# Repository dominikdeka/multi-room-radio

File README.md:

**enable Network at Boot**

`sudo raspi-config`
System Options->Network at Boot (enabled)

**print temperature alias**

`alias temp='vcgencmd measure_temp'`

**install gpio listener**

`sudo pip3 install websockets`
add to /etc/rc.local
`/home/pi/python_scripts/multi-room-radio/start.sh &> /tmp/rc.local.log`

**install mopidy**

https://docs.mopidy.com/en/latest/installation/debian/#install-from-apt-mopidy-com
```
sudo adduser mopidy video
```

https://mopidy.com/ext/
```
sudo python3 -m pip install Mopidy-TuneIn
sudo python3 -m pip install Mopidy-YouTube
sudo python3 -m pip install youtube-dl
sudo python3 -m pip install Mopidy-Iris
sudo python3 -m pip install Mopidy-Mobile
sudo python3 -m pip install Mopidy-SoundCloud
sudo python3 -m pip install Mopidy-Tidal

sudo chmod 755 /media/pi
copy mopidy.conf to /etc/mopidy/
```
https://docs.mopidy.com/en/latest/running/service/

```
pi@raspberrypi:~ $ aplay -L
(...)
hdmi:CARD=vc4hdmi,DEV=0
    vc4-hdmi, MAI PCM i2s-hifi-0
    HDMI Audio Output
(...)
```
--->
```
pi@raspberrypi:~ $ sudo vi /etc/mopidy/mopidy.conf
[audio]
output = alsasink device=hdmi:vc4hdmi
```

```
systemctl list-units --type=mount
```
--->
```
pi@raspberrypi:~ $ sudo vi /usr/lib/systemd/system/mopidy.service
[Unit]
(...)
After=media-pi-KINGSTON.mount
(...)
```

**crontab**

use backuped crontab

**hdmi blink**

turn it off

**websockets**

add content of https://github.com/dominikdeka/multi-room-radio/blob/master/index.html to
/usr/local/lib/python2.7/dist-packages/mopidy_mobile/www/index.html

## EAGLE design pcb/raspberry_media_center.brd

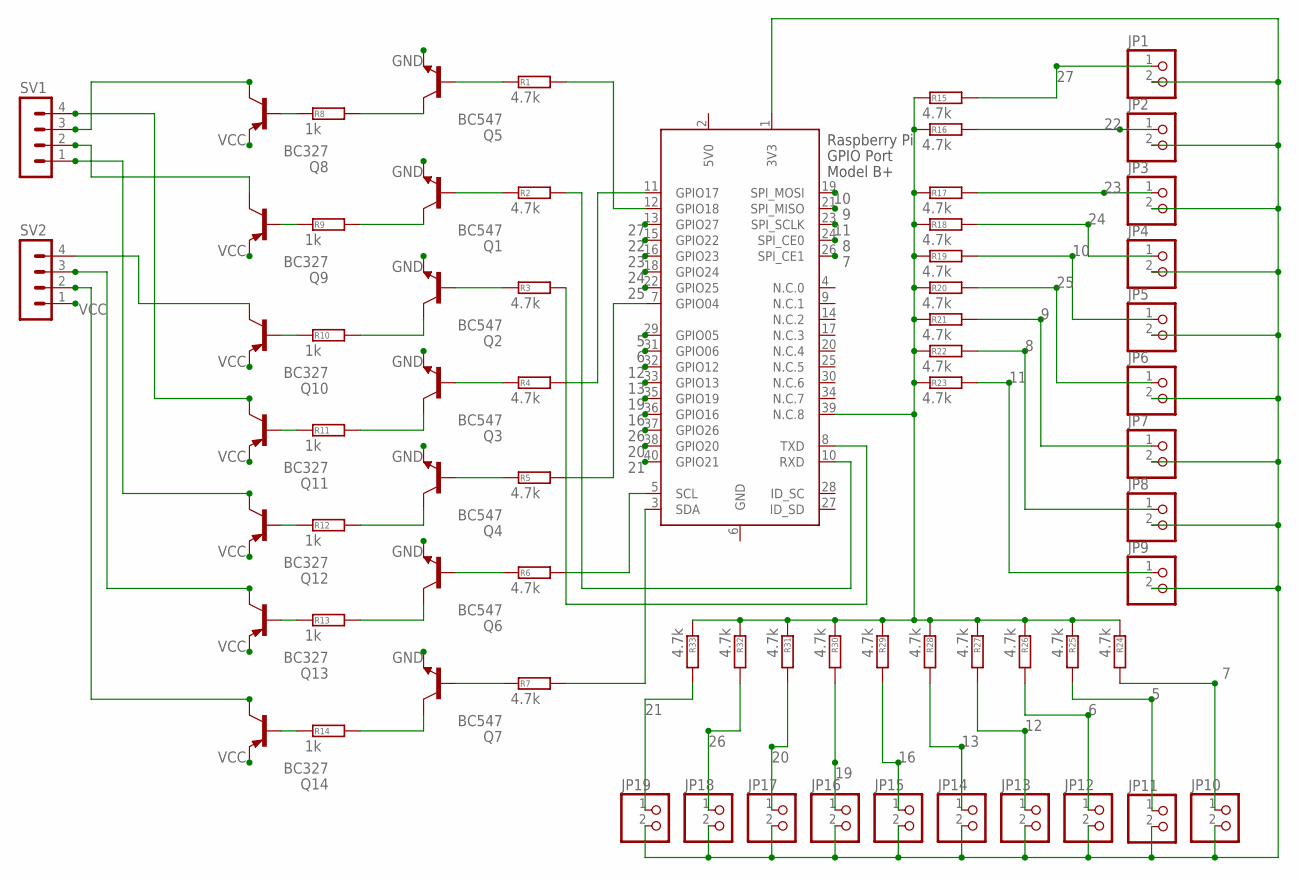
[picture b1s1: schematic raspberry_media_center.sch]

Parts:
JP1, JP2, JP3, JP4, JP5, JP6, JP7, JP8, JP9, JP10, JP11, JP12, JP13, JP14, JP15, JP16, JP17, JP18, JP19: PINHD-1X2; 1X02
Q1, Q2, Q3, Q4, Q5, Q6, Q7: BC547; TO92
Q8, Q9, Q10, Q11, Q12, Q13, Q14: BC327; TO92-EBC
R1, R2, R3, R4, R5, R6, R7: 4.7k; 0204/7
R8, R9, R10, R11, R12, R13, R14: 1k; 0204/7
R15, R16, R17, R18, R19, R20, R21, R22, R23, R24, R25, R26, R27, R28, R29, R30, R31, R32, R33: 4.7k; 0207/15
SV1, SV2: MA04-1
X1: RASPI_BOARD_B+_E0; RASPI_BOARD_B+_EDGES_0DRILL

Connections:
5: JP11.1, R25.2, X1.29 (GPIO05)
5V0: X1.2 (5V0)
6: JP12.1, R26.2, X1.31 (GPIO06)
7: JP10.1, R24.2, X1.26 (SPI_CE1)
8: JP8.1, R22.2, X1.24 (SPI_CE0)
9: JP7.1, R21.2, X1.21 (SPI_MISO)
10: JP5.1, R19.2, X1.19 (SPI_MOSI)
11: JP9.1, R23.2, X1.23 (SPI_SCLK)
12: JP13.1, R27.2, X1.32 (GPIO12)
13: JP14.1, R28.2, X1.33 (GPIO13)
16: JP15.1, R29.2, X1.36 (GPIO16)
19: JP16.1, R30.2, X1.35 (GPIO19)
20: JP17.1, R31.2, X1.38 (GPIO20)
21: JP19.1, R33.2, X1.40 (GPIO21)
22: JP2.1, R16.2, X1.15 (GPIO22)
23: JP3.1, R17.2, X1.16 (GPIO23)
24: JP4.1, R18.2, X1.18 (GPIO24)
25: JP6.1, R20.2, X1.22 (GPIO25)
26: JP18.1, R32.2, X1.37 (GPIO26)
27: JP1.1, R15.2, X1.13 (GPIO27)
GND: Q1.1 (E), Q2.1 (E), Q3.1 (E), Q4.1 (E), Q5.1 (E), Q6.1 (E), Q7.1 (E), X1.6 (GND)
unnamed: R7.2, X1.3 (SDA)
unnamed: R6.2, X1.5 (SCL)
unnamed: R5.2, X1.7 (GPIO04)
unnamed: R4.2, X1.11 (GPIO17)
unnamed: R3.2, X1.8 (TXD)
unnamed: R2.2, X1.10 (RXD)
unnamed: R1.2, X1.12 (GPIO18)
unnamed: Q5.2 (B), R1.1
unnamed: Q1.2 (B), R2.1
unnamed: Q2.2 (B), R3.1
unnamed: Q3.2 (B), R4.1
unnamed: Q4.2 (B), R5.1
unnamed: Q6.2 (B), R6.1
unnamed: Q7.2 (B), R7.1
unnamed: Q1.3 (C), R9.2
unnamed: Q5.3 (C), R8.2
unnamed: Q6.3 (C), R13.2
unnamed: Q4.3 (C), R12.2
unnamed: Q3.3 (C), R11.2
unnamed: Q2.3 (C), R10.2
unnamed: Q7.3 (C), R14.2
unnamed: Q8.B, R8.1
unnamed: Q9.B, R9.1
unnamed: Q10.B, R10.1
unnamed: Q11.B, R11.1
unnamed: Q12.B, R12.1
unnamed: Q13.B, R13.1
unnamed: Q14.B, R14.1
unnamed: R15.1, R16.1, R17.1, R18.1, R19.1, R20.1, R21.1, R22.1, R23.1, R24.1, R25.1, R26.1, R27.1, R28.1, R29.1, R30.1, R31.1, R32.1, R33.1, X1.39 (N.C.8)
unnamed: JP1.2, JP2.2, JP3.2, JP4.2, JP5.2, JP6.2, JP7.2, JP8.2, JP9.2, JP10.2, JP11.2, JP12.2, JP13.2, JP14.2, JP15.2, JP16.2, JP17.2, JP18.2, JP19.2, X1.1 (3V3)
unnamed: Q14.C, SV2.2
unnamed: Q13.C, SV2.3
unnamed: Q12.C, SV1.1
unnamed: Q11.C, SV1.4
unnamed: Q10.C, SV2.4
unnamed: Q8.C, SV1.3
unnamed: Q9.C, SV1.2
VCC: Q8.E, Q9.E, Q10.E, Q11.E, Q12.E, Q13.E, Q14.E, SV2.1

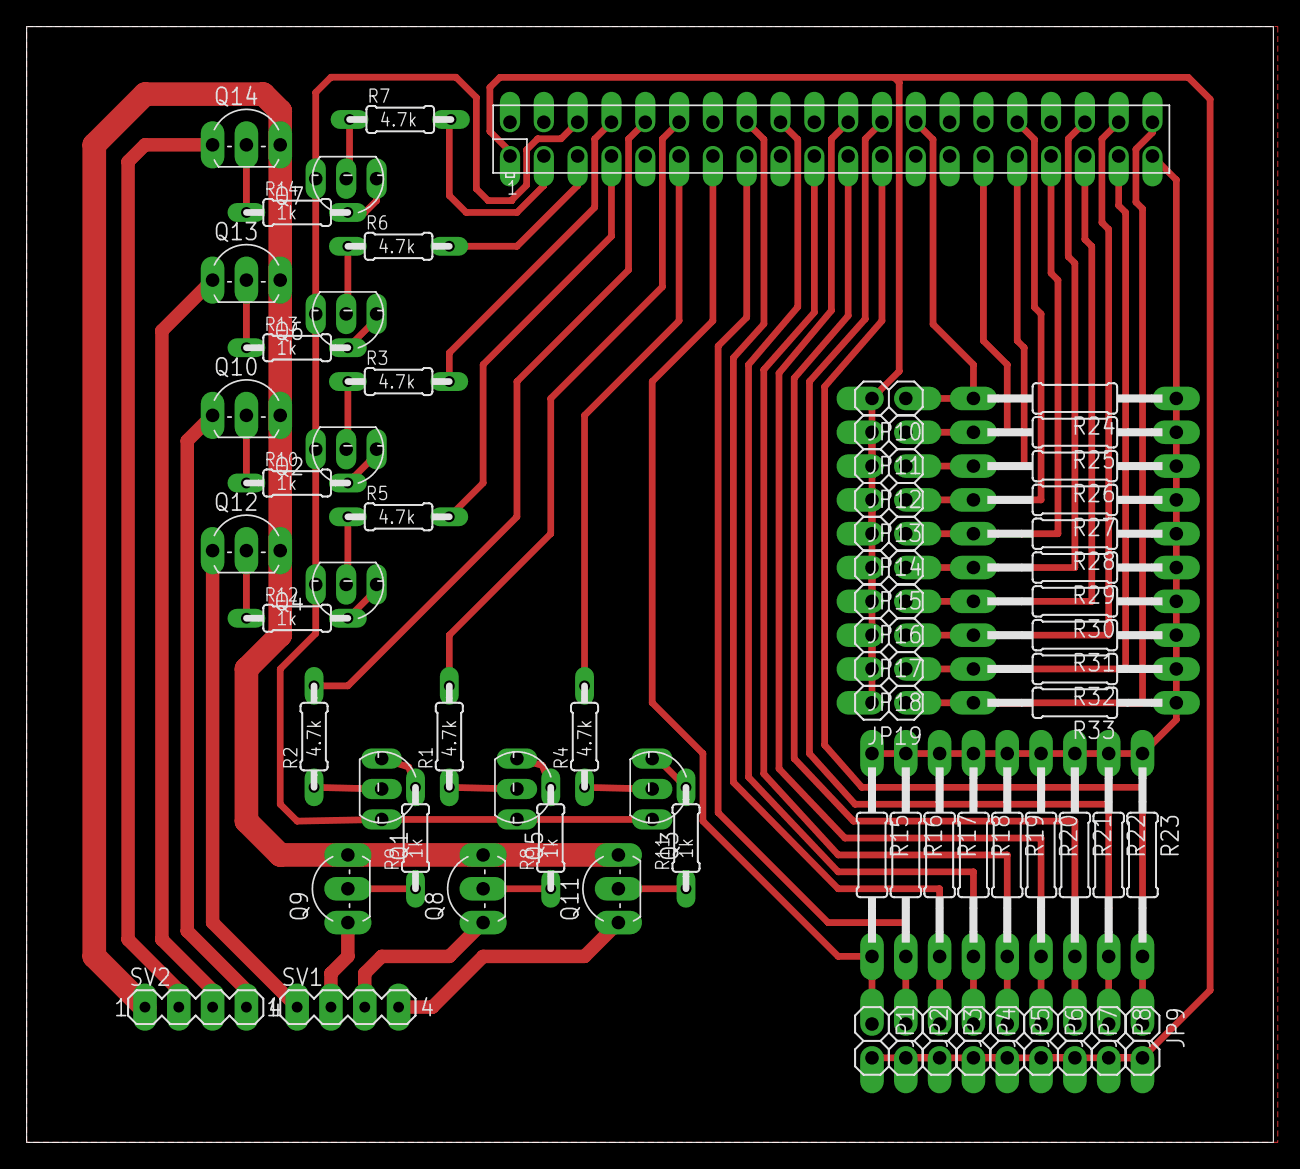
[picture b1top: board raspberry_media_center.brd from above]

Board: 2 copper layers, 93.7 x 83.8 mm, 69 parts (0 on the bottom side), 58 nets.

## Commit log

2018-06-18 websockets introduced
2018-08-17 setup + l&f
2018-08-31 start script added
2018-09-17 more functions
2018-09-18 mic function added
2018-09-24 new playlists features, startup script corrections
2019-03-27 wakeup added + fix
2019-11-04 new wakeup set and new room added
2019-11-10 reconnecting support on mobile devices
2020-05-06 gpio reffactoring, new functions added
2020-05-08 pcb added
2020-08-17 wake up/alarm
2021-11-11 new features
2021-12-02 new features added
2022-09-15 python upgrade, os upgrade, mopidy upgrade + README
2022-09-15 README update
2023-02-28 minor changes
2024-06-17 gitignore, ws_client changes
